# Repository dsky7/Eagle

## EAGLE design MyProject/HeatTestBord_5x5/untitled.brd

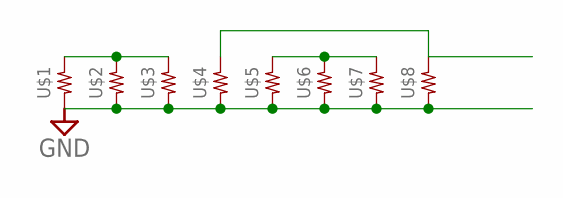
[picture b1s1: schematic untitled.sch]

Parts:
U$1, U$2, U$3, U$4, U$5, U$6, U$7, U$8: RESISTOR__SMD; 1608

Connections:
GND: U$1.1, U$2.1, U$3.1, U$4.1, U$5.1, U$6.1, U$7.1, U$8.1
unnamed: U$1.2, U$2.2, U$3.2
unnamed: U$5.2, U$6.2, U$7.2
unnamed: U$4.2, U$8.2

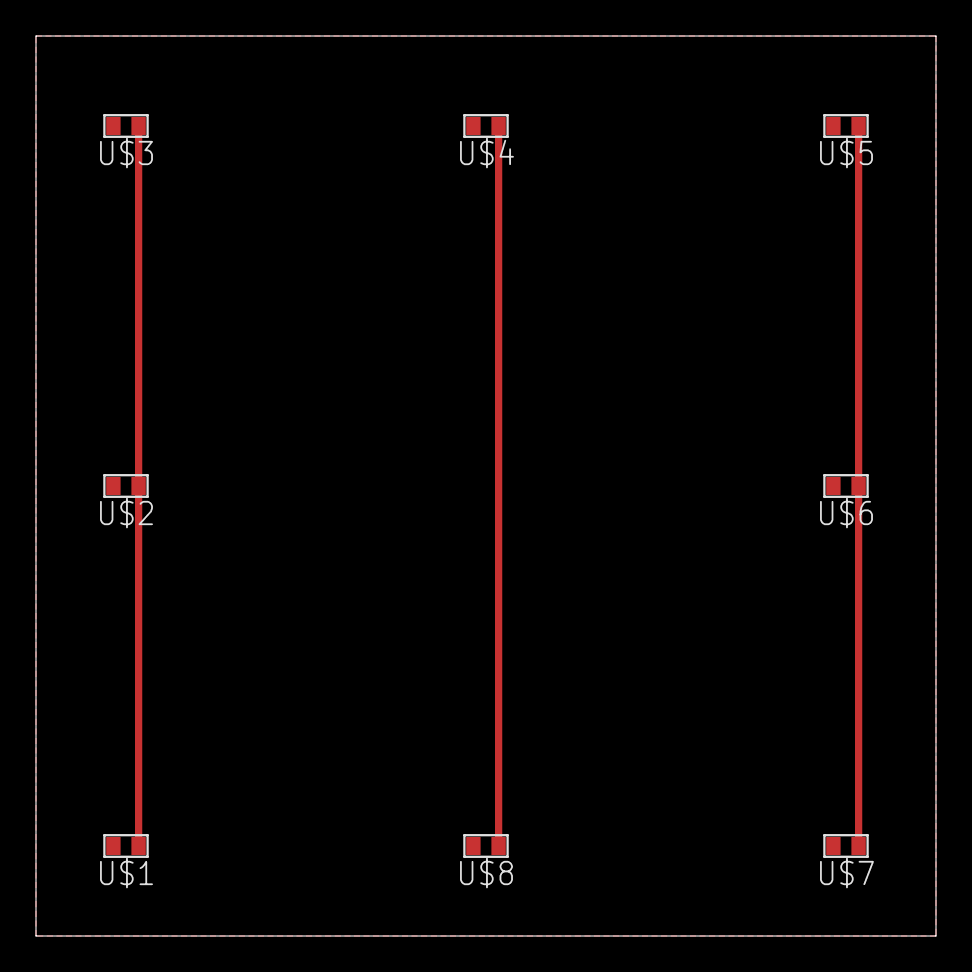
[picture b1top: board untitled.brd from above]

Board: 2 copper layers, 50.0 x 50.0 mm, 8 parts (0 on the bottom side), 4 nets.

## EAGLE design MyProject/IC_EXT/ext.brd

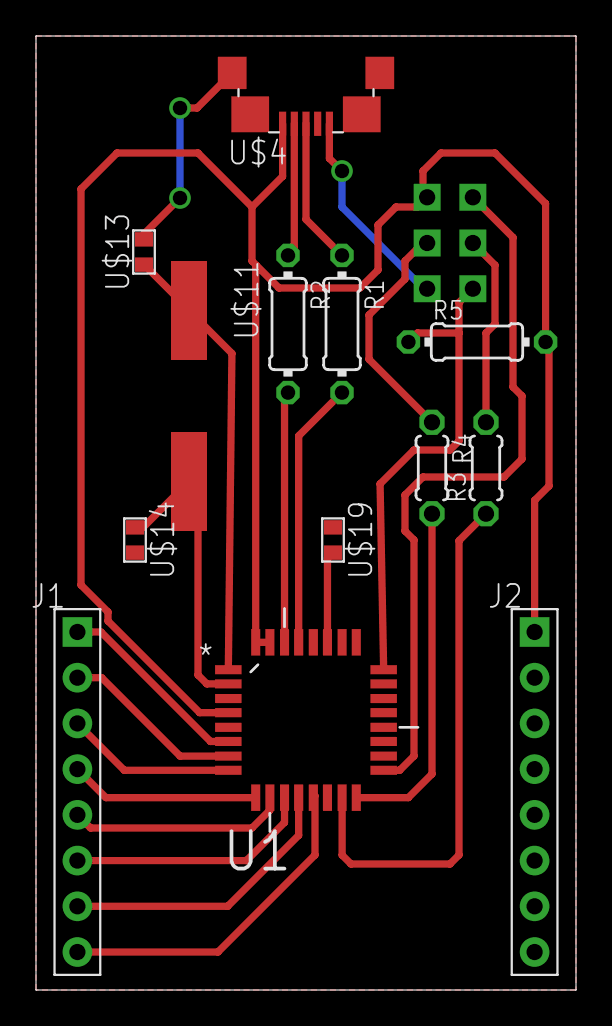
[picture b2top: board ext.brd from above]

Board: 2 copper layers, 30.0 x 53.0 mm, 14 parts (1 on the bottom side), 23 nets.

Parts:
J1, J2: 8P-2.54
R1, R2, R5: 0204/7
R3, R4: 0204/5
U1: ATMEGA32U2-AU; QFP80P900X900X120-32N
U$4: MICRO-USB-SHIELD-ZX62R-B-5P; ZX62R-B-5P
U$7: ICSP
U$11: CSM-7X-DU
U$13, U$14, U$19: 1608

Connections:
+5V: J2.1, R5.2, U1.4, U1.31, U1.32, U$4.1, U$7.2
D+: R1.1, U$4.3
D-: R2.1, U$4.2
GND: J2.2, U1.3, U1.28, U$4.5, U$4.M1, U$4.M2, U$4.M3, U$4.M4, U$7.6, U$13.P$2, U$14.P$2, U$19.P$1
MISO: U1.17, U$7.1
MOSI: R4.2, U1.16
unnamed: J1.2, U1.7
unnamed: J1.3, U1.8
unnamed: J1.4, U1.9
unnamed: J1.5, U1.10
unnamed: J1.6, U1.11
unnamed: J1.7, U1.12
unnamed: J1.8, U1.13
unnamed: J1.1, U1.6
unnamed: R1.2, U1.29
unnamed: R2.2, U1.30
unnamed: R3.2, U$7.3
unnamed: R4.1, U$7.4
unnamed: U1.27, U$19.P$2
RESET: R5.1, U1.24, U$7.5
SCLK: R3.1, U1.15
XTAL1: U1.1, U$11.1, U$13.P$1
XTAL2: U1.2, U$11.2, U$14.P$1

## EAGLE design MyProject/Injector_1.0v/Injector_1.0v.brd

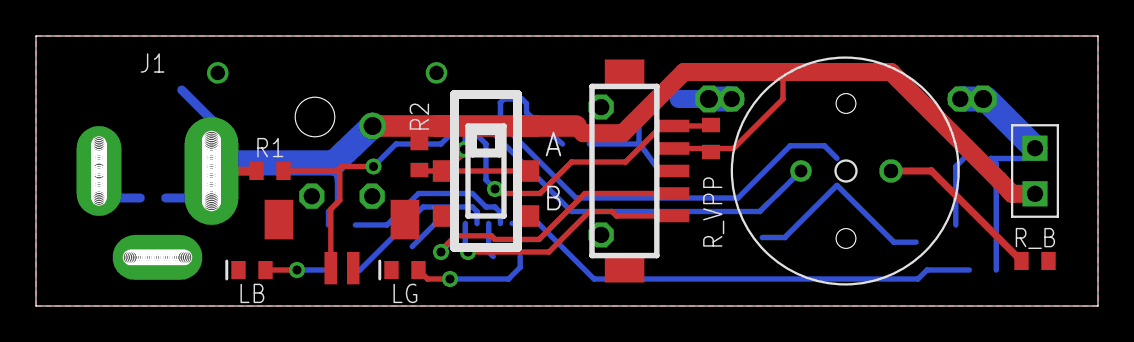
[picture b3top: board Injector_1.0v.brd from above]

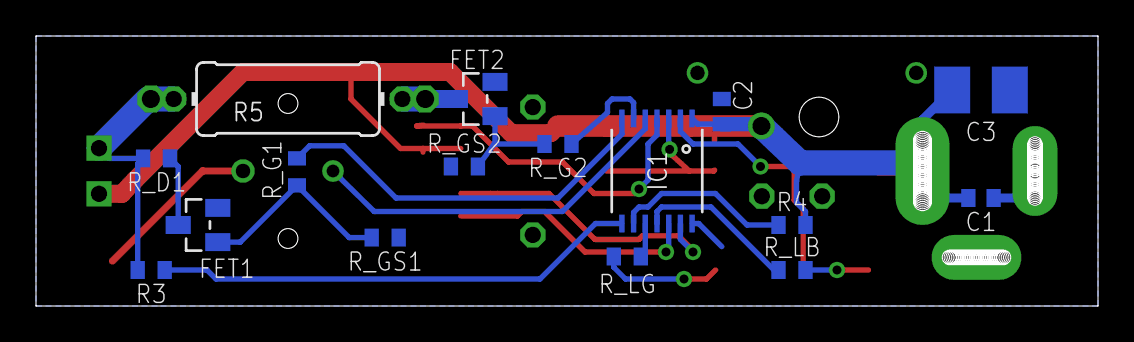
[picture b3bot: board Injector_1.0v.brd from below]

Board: 2 copper layers, 59.0 x 15.0 mm, 30 parts (17 on the bottom side), 22 nets.

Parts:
BUZZER: PKM13EPYH
C1, C2: 1608
C3: 3225
CN1: DF13-5P-1.25V; DF13C-5P-1.25V
CN2: DF13-2P-1.25V; DF13C-2P-1.25V
CN3: PIN_HEADER_2; PIN_HEADER_2S
DRILEGEND: DRILEGEND
FET1, FET2: CHIP_FET; SOT23
IC1: PIC16F1823; TSSOP
J1: 2DC-0005X; 2DC-0005D
LB: CHIPLED; 1608
LG: CHIPLED; 1608
R1, R2, R3, R4: 1608
R5: 0411/12
R6: P0613/15
R_B: 1608
R_D1: 1608
R_G1, R_G2: 1608
R_GS1, R_GS2: 1608
R_LB: 1608
R_LG: 1608
R_VPP: 1608
SW1: SSSS213202; SSSS2

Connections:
+5V: C1.P$2, C2.P$2, C3.P$2, CN1.P$2, CN3.P$2, IC1.1, J1.1, R1.2, R2.2, R4.1, R_VPP.2, SW1.1, SW1.1-
G1: IC1.7, R_G1.2
G2: IC1.6, R_G2.2
GND: C1.P$1, C2.P$1, C3.P$1, CN1.M$0, CN1.M$1, CN1.P$3, CN1.P$6, CN1.P$7, CN2.1, CN2.G1, CN2.G2, CN2.M$0, CN2.M$1, FET1.2, FET2.2, IC1.14, J1.2, LB.2, LG.2, R_B.1, R_GS1.2, R_GS2.2, SW1.3, SW1.3-
ICSP_CLK: CN1.P$5, IC1.12
ICSP_DATA: CN1.P$4, IC1.13
MCLR: CN1.P$1, IC1.4, R_VPP.1
unnamed: FET1.1, R_G1.1, R_GS1.1
unnamed: FET2.1, R_G2.1, R_GS2.1
unnamed: FET1.3, R_D1.2
unnamed: FET2.3, R5.1, R6.1
unnamed: BUZZER.P$1, IC1.5
unnamed: BUZZER.P$2, R_B.2
unnamed: CN2.2, IC1.2, R1.1
unnamed: IC1.8, R3.2
unnamed: IC1.9, R4.2
unnamed: LB.1, R_LB.1
unnamed: CN3.P$1, R3.1, R5.2, R6.2, R_D1.1
unnamed: LG.1, R_LG.1
RA2: IC1.11, R_LB.2
RA4: IC1.3, R2.1, SW1.2, SW1.2-
RC0: IC1.10, R_LG.2

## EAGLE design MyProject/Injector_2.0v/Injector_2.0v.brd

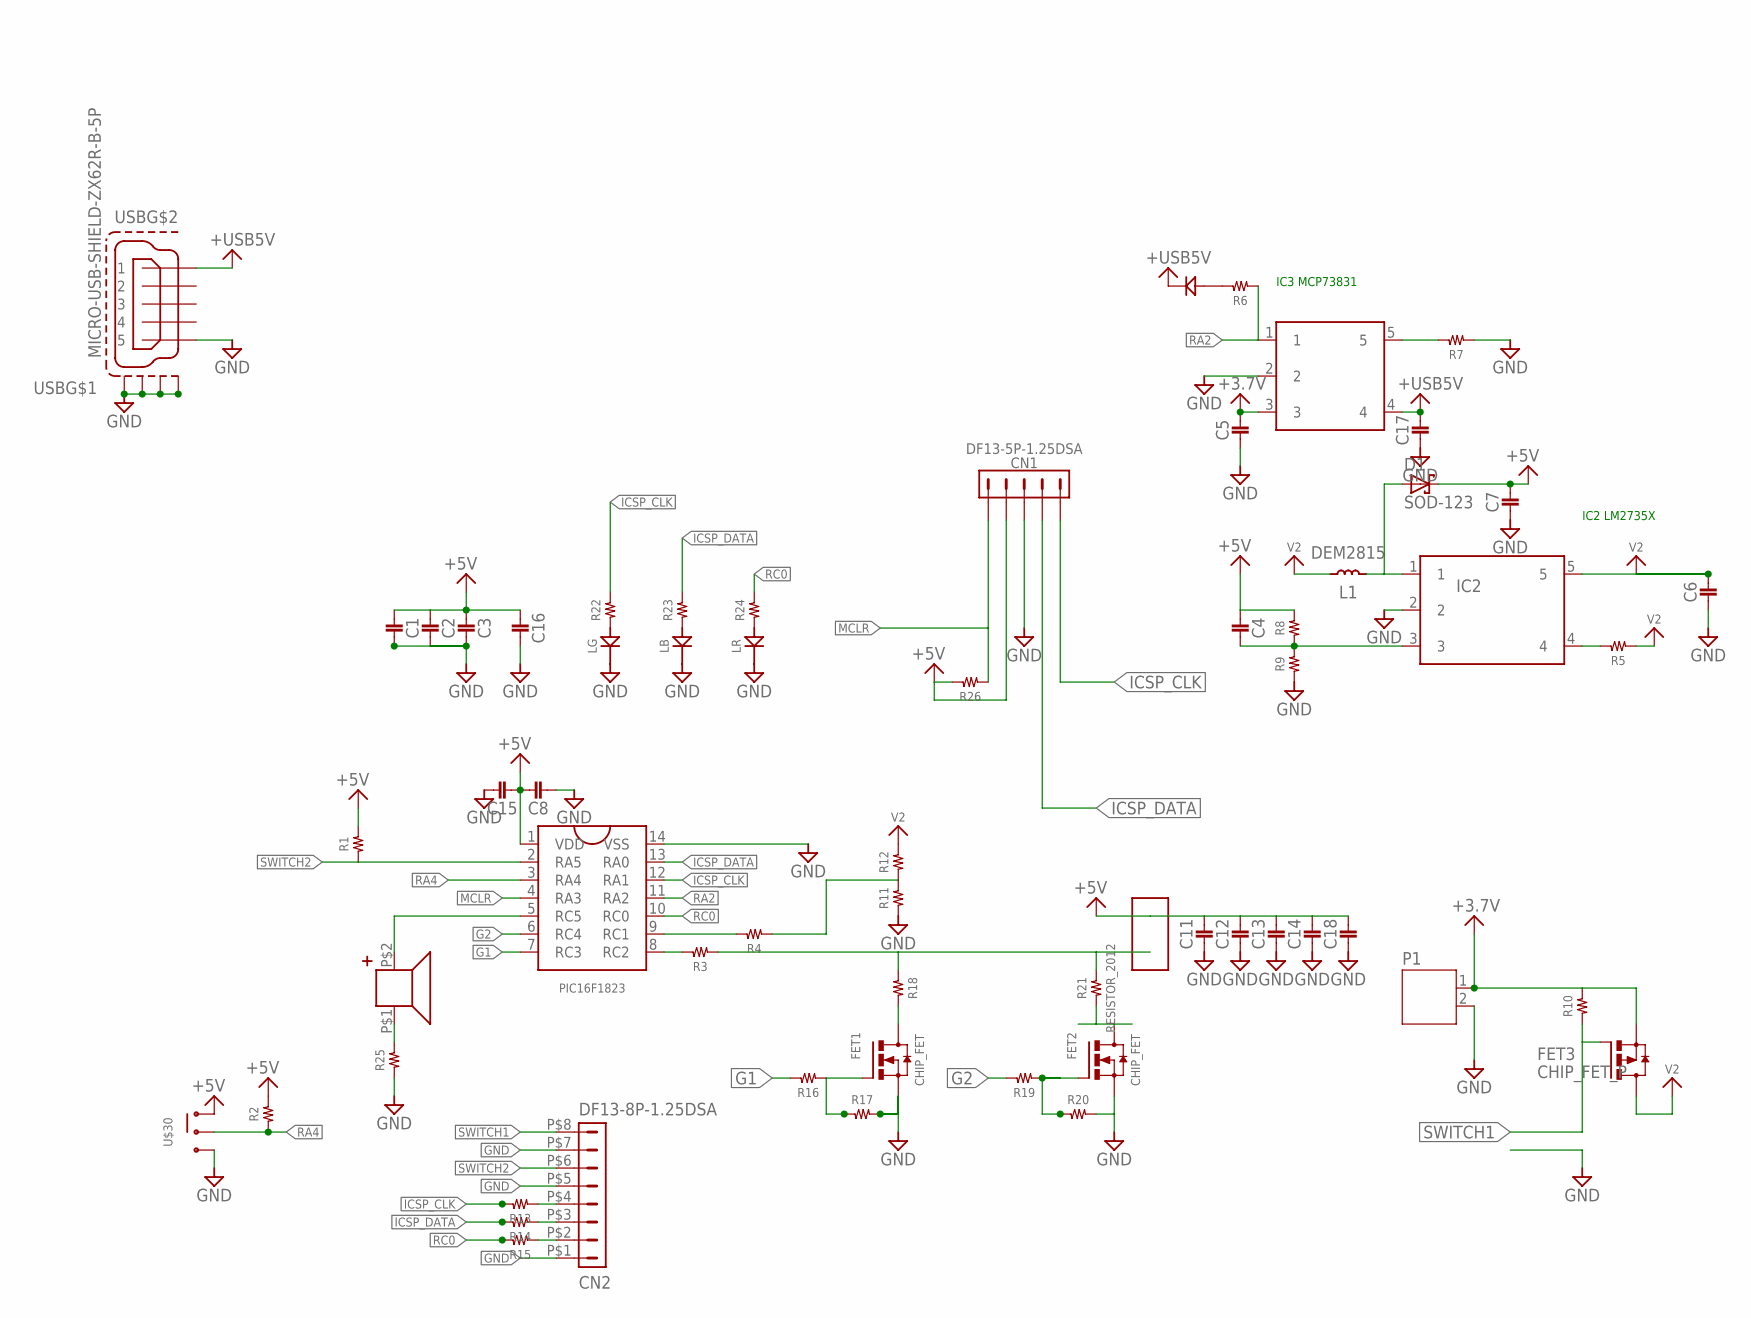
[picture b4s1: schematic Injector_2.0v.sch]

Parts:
C1, C2, C3, C4, C5, C6, C7, C8, C11, C12, C13, C14, C15, C16, C17, C18: 1608
CN1: DF13-5P-1.25DSA
CN2: DF13-8P-1.25DSA
D1: SOD-123; SOD_123
FET1, FET2: CHIP_FET; SOT23
FET3: CHIP_FET_P; SOT23
IC1: PIC16F1823; TSSOP
IC2: LM2735; SOT23-5L
IC3: MCP73831; SOT23-5L
L1: DEM2815
LB: CHIPLED; 1608
LG: CHIPLED; 1608
LR: CHIPLED; 1608
P1: JST-PH2
R1, R2, R3, R4, R5, R6, R7, R8, R9, R10, R11, R12, R13, R14, R15, R16, R17, R18, R19, R20, R22, R23, R24, R25, R26: RESISTOR__SMD; 1608
R21: RESISTOR_2012; 2012
ST: 1608
U$15: PKLCS1212E4001
U$16: PIN_HEADER_2_LARGE; PIN_HEADER_2S_LARGE
U$30: SS12D01G4
USB: MICRO-USB-SHIELD-ZX62R-B-5P; ZX62R-B-5P

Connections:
+3.7V: C5.P$1 (1), FET3.2 (S), IC3.3, P1.1, R10.2
+5V: C1.P$2 (2), C2.P$2 (2), C3.P$2 (2), C4.P$2 (2), C7.P$1 (1), C8.P$1 (1), C11.P$1 (1), C12.P$1 (1), C13.P$1 (1), C14.P$1 (1), C15.P$2 (2), C16.P$1 (1), C18.P$1 (1), CN1.P$2 (2), D1.C, IC1.1 (VDD), R1.2, R2.2, R8.2, R26.2, U$16.P$2, U$30.1
+USB5V: C17.P$1 (1), IC3.4, ST.2 (K), USB.1
G1: IC1.7 (RC3), R16.2
G2: IC1.6 (RC4), R19.2
GND: C1.P$1 (1), C2.P$1 (1), C3.P$1 (1), C5.P$2 (2), C6.P$2 (2), C7.P$2 (2), C8.P$2 (2), C11.P$2 (2), C12.P$2 (2), C13.P$2 (2), C14.P$2 (2), C15.P$1 (1), C16.P$2 (2), C17.P$2 (2), C18.P$2 (2), CN1.P$3 (3), CN2.P$1 (1), CN2.P$5 (5), CN2.P$7 (7), FET1.2 (S), FET2.2 (S), IC1.14 (VSS), IC2.2, IC3.2, LB.2 (K), LG.2 (K), LR.2 (K), P1.2, R7.1, R9.1, R11.1, R17.2, R20.2, R25.1, U$30.3, USB.5, USB.M1 (S1), USB.M2 (S2), USB.M3 (S3), USB.M4 (S4)
ICSP_CLK: CN1.P$5 (5), IC1.12 (RA1), R13.2, R22.2
ICSP_DATA: CN1.P$4 (4), IC1.13 (RA0), R14.2, R23.2
MCLR: CN1.P$1 (1), IC1.4 (RA3), R26.1
unnamed: FET1.1 (G), R16.1, R17.1
unnamed: FET2.1 (G), R19.1, R20.1
unnamed: FET1.3 (D), R18.2
unnamed: FET2.3 (D), R21.1
unnamed: IC1.5 (RC5), U$15.P$2 (PLUS)
unnamed: R25.2, U$15.P$1 (MINUS)
unnamed: IC1.8 (RC2), R3.2
unnamed: IC1.9 (RC1), R4.2
unnamed: LG.1 (A), R22.1
unnamed: R3.1, R18.1, R21.2, U$16.P$1
unnamed: LB.1 (A), R23.1
unnamed: D1.A, IC2.1, L1.P$2 (2)
unnamed: IC3.5, R7.2
unnamed: LR.1 (A), R24.1
unnamed: C4.P$1 (1), IC2.3, R8.1, R9.2
unnamed: IC2.4, R5.2
unnamed: R4.1, R11.2, R12.1
unnamed: CN2.P$4 (4), R13.1
unnamed: CN2.P$3 (3), R14.1
unnamed: CN2.P$2 (2), R15.1
unnamed: R6.2, ST.1 (A)
RA2: IC1.11 (RA2), IC3.1, R6.1
RA4: IC1.3 (RA4), R2.1, U$30.2
RC0: IC1.10 (RC0), R15.2, R24.2
SWITCH1: CN2.P$8 (8), FET3.1 (G), R10.1
SWITCH2: CN2.P$6 (6), IC1.2 (RA5), R1.1
V2: C6.P$1 (1), FET3.3 (D), IC2.5, L1.P$1 (1), R5.1, R12.2

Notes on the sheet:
IC3 MCP73831
IC2 LM2735X

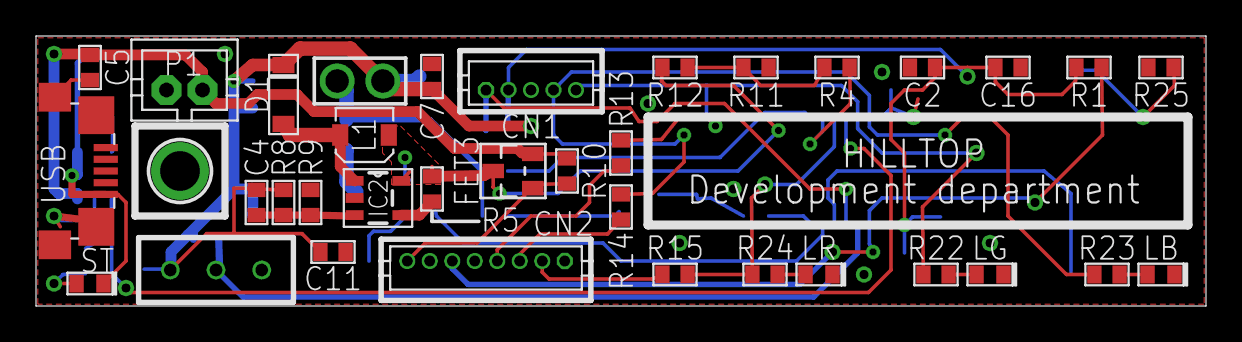
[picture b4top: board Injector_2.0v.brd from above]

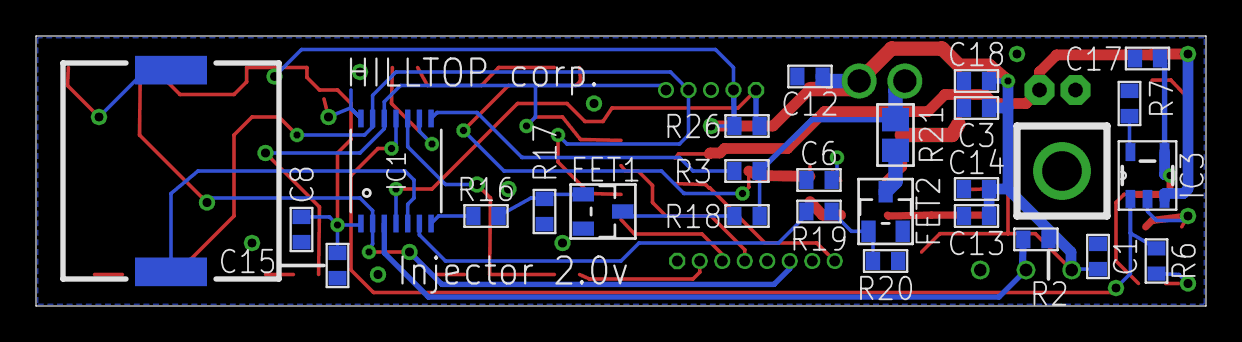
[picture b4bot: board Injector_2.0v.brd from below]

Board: 2 copper layers, 65.0 x 15.0 mm, 62 parts (26 on the bottom side), 36 nets.

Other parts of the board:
DRILEGEND: DRILEGEND

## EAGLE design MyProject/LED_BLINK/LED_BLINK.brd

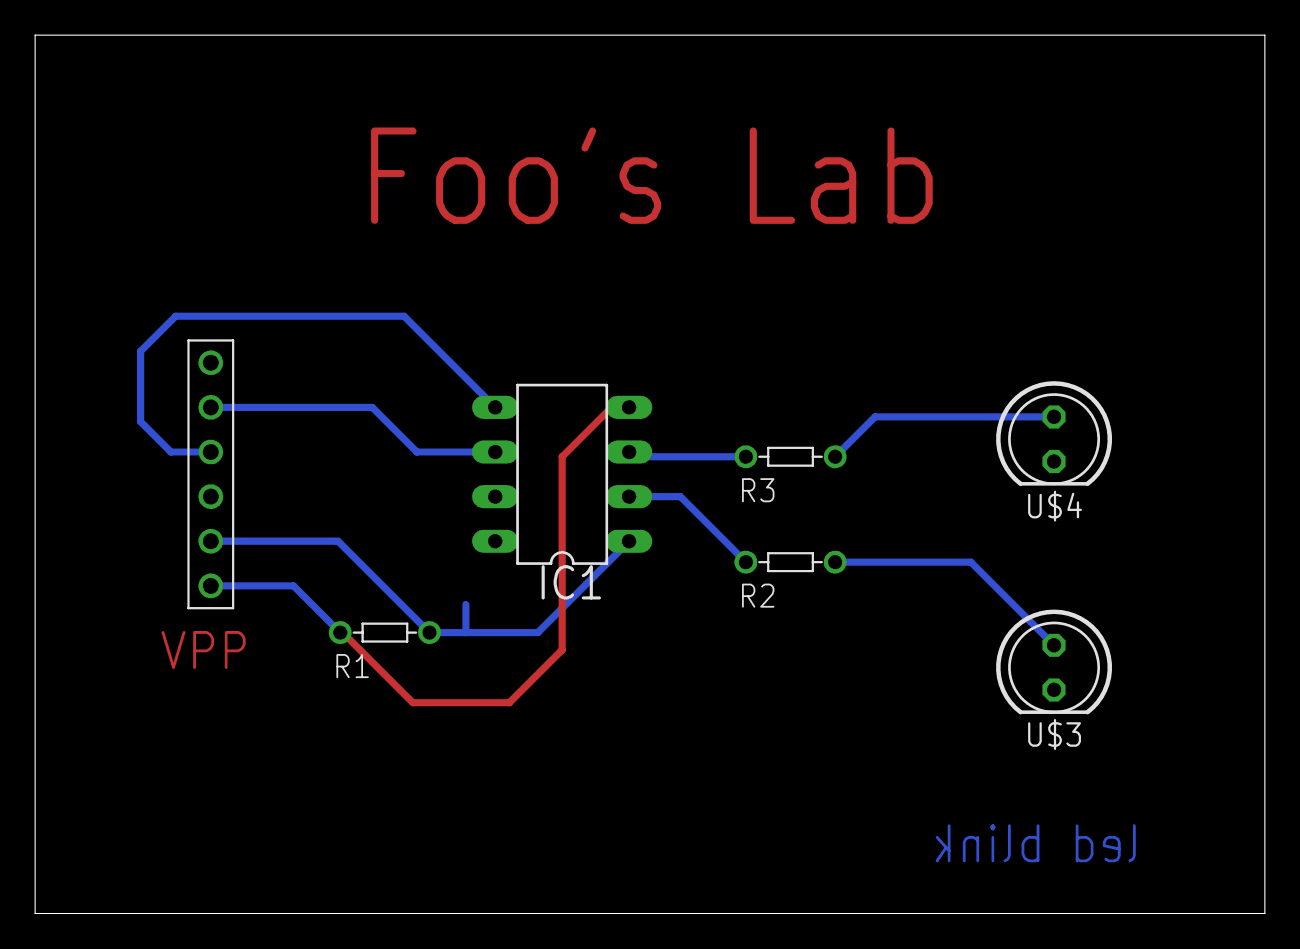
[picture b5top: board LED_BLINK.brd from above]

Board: 2 copper layers, 70.0 x 50.0 mm, 8 parts (1 on the bottom side), 9 nets.

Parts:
IC1: PIC12F683P; DIL8
R1, R2, R3: 1/8R
U$3, U$4: 5MMLED; 5MM
U$9: 1608
U$11: PIN_HEADER_6

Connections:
+5V: IC1.1, R1.P$2, U$9.P$1, U$11.2
CLK: IC1.6, U$11.5
DAT: IC1.5, U$11.4
GND: IC1.8, U$3.K, U$4.K, U$9.P$2, U$11.3
unnamed: R2.P$2, U$3.A
unnamed: R3.P$2, U$4.A
unnamed: IC1.2, R2.P$1
unnamed: IC1.3, R3.P$1
VPP: IC1.4, R1.P$1, U$11.1

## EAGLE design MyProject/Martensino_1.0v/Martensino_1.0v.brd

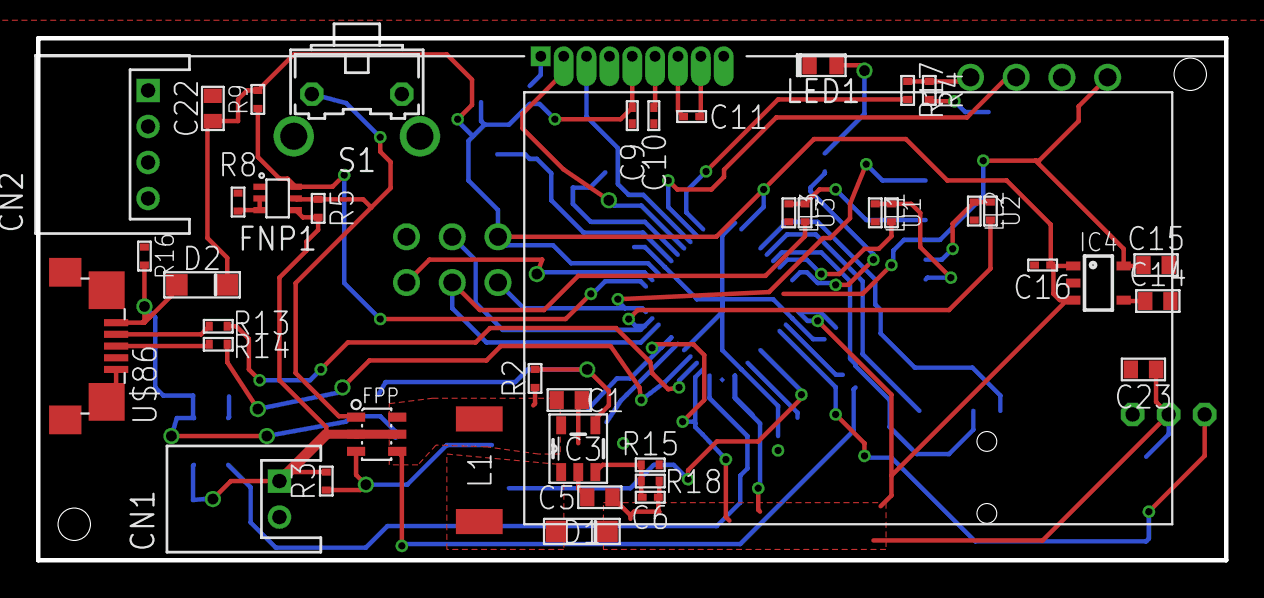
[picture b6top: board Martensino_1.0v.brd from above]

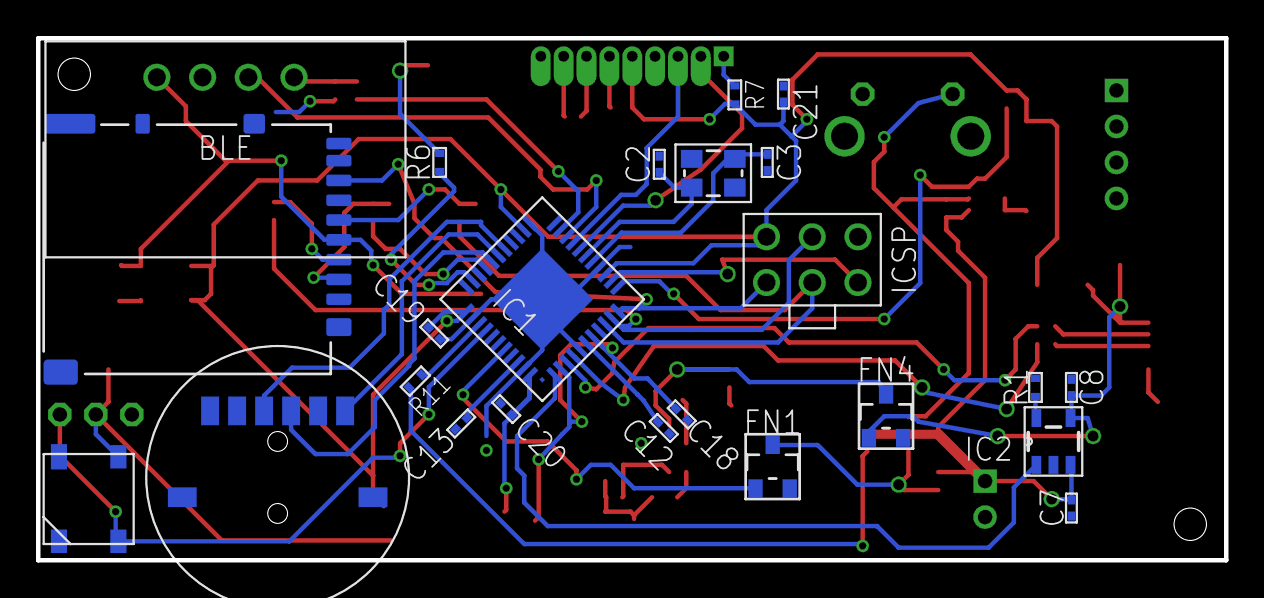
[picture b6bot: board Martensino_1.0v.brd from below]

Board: 2 copper layers, 66.0 x 29.0 mm, 68 parts (24 on the bottom side), 49 nets.

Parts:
BLE: BLE_SERIAL2_NO_HOLE; BLESERIAL2_NO_HOLE
C1, C5: 22uF; 1608
C2, C3: 10pF; 1005
C6: 1nF; 1005
C7, C8: 4.7uF; 1005
C9, C10, C11: 1005
C12, C16: 1uF; 1005
C13, C18, C19, C20, C21: 0.1uF; 1005
C14: 0.01uF; 1608
C15, C23: 10uF; 1608
C22: 47uF; 1608
CN1: S2B-PH-K-S
CN2: S4B-PH-K-S
D1, D2: SOD-123; SOD_123
FN1, FN4: CHIP_FET; SOT23
FNP1: SI1553CDL; SOT363
FPP: FDC6506P; SOT23-6
IC1: ATMEGA32U4; QFN-44-7X7
IC2: MCP73831; SOT23-5L
IC3: LM2735; SOT23-5L
IC4: TAR5SB; SSOP5-P-0.95
L1: D63; TOKO
LED1: CHIPLED; 1608
LED2: NEO_FLAT
LL1: 3k; 1005
LL2, LL3: 3K; 1005
R1: 2K; 1005
R2: 100K; 1005
R3, R5, R8, R9, R15, R16: 10K; 1005
R4: 1.5k; 1005
R6: 330; 1005
R7: RESISTOR_1005; 1005
R11, R17: 1K; 1005
R13, R14: 22; 1005
R18: 30k; 1005
S1: B3F-31XX
U1, U3: 2K; 1005
U2: 2k; 1005
U$3: ICSP
U$8: LIPO400MAH
U$30: 3PIN_HALF; 3PIN_INT_HALF
U$45: DM3AT-SF-PEJ
U$68: LCD_I2C_AQM; AQM1602
U$86: MICRO-USB-KYORITU; ZX62R-B-5P
U$90: TMHU28
XTAL: FA-238

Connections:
+3.3V: BLE.4, C15.P$1, IC4.5, U$45.4
+3.7V: C1.P$1, FPP.4, FPP.6, IC3.5, L1.1, R2.2, R11.2
+5V: C5.P$1, C6.1, C9.1, C16.1, C18.1, C19.1, C20.1, C21.1, C22.P$1, C23.P$1, D1.C, D2.C, IC1.2, IC1.7, IC1.14, IC1.24, IC1.34, IC1.44, IC4.1, IC4.3, LED2.1, R7.2, R9.2, R18.2, U$3.2, U$30.2, U$68.P$5
+USB5V: C8.1, D2.A, FN4.1, IC2.4, R16.2, U$86.5
A1: IC1.37, LED2.4, U$30.3
A4: FN1.1, IC1.40
ADC0: IC1.36, R11.1
ATOM: BLE.1, R4.2, R17.1
D0: BLE.2, IC1.20
D1: IC1.21, R17.2
D2: IC1.19, U$68.P$3
D3: IC1.18, U$68.P$2
D6: IC1.27, U$90.3
D7: IC1.1, IC2.1
D8: IC1.28, U$90.1
D9: IC1.29, U$90.T
D10: IC1.30, U1.2
D11: FNP1.6, IC1.12, R9.1
D13: IC1.32, R6.2
D+: R14.2, U$86.3
D-: R13.2, U$86.4
DL: D1.A, IC3.1, L1.2
FB: C6.2, IC3.3, R15.2, R18.1
GND: BLE.3, C1.P$2, C2.2, C3.2, C5.P$2, C7.2, C8.2, C9.2, C10.2, C12.1, C13.2, C14.P$2, C15.P$2, C16.2, C18.2, C19.2, C20.2, C21.2, C22.P$2, C23.P$2, CN1.2, FN1.2, FN4.2, FNP1.1, IC1.5, IC1.15, IC1.23, IC1.35, IC1.43, IC1.TH, IC2.2, IC3.2, IC4.2, LED1.2, LED2.3, LL1.2, LL2.2, LL3.2, R1.1, R4.1, R8.1, R15.1, R16.1, S1.1, U$3.6, U$30.1, U$45.6, U$45.GND1, U$45.GND2, U$45.GND3, U$45.GND4, U$68.P$4, U$86.1, U$86.M1, U$86.M2, U$86.M3, U$86.M4, U$90.C, XTAL.2, XTAL.4
MISO: IC1.11, U$3.1, U$45.7
MOSI: IC1.10, U2.2, U$3.4
unnamed: LED1.1, R6.1
unnamed: IC2.5, R1.2
unnamed: FN4.3, IC3.4, R2.1
unnamed: R7.1, U$68.P$1
unnamed: LL3.1, U3.1, U$45.5
unnamed: FN1.3, FPP.3, R3.1
unnamed: C3.1, IC1.16, XTAL.1
unnamed: IC1.3, R13.1
unnamed: C13.1, IC1.42
unnamed: C2.1, IC1.17, XTAL.3
unnamed: LL2.1, U2.1, U$45.3
unnamed: LL1.1, U1.1, U$45.2
unnamed: C12.2, IC1.6
unnamed: IC1.4, R14.1
unnamed: C14.P$1, IC4.4
unnamed: C10.1, U$68.P$6
unnamed: C11.1, U$68.P$7
unnamed: C11.2, U$68.P$8
RESET: IC1.13, U$3.5
SCLK: IC1.9, U3.2, U$3.3
SIG: FNP1.2, FNP1.3, R8.2
SWSIG: FNP1.5, FPP.1, R5.1, S1.2
V2: C7.1, CN1.1, FNP1.4, FPP.2, FPP.5, IC2.3, R3.2, R5.2

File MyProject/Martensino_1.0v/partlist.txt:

Partlist

Exported from Martensino_1.0v.brd at 2016/03/08 19:01

EAGLE Version 7.5.0 Copyright (c) 1988-2015 CadSoft

Assembly variant: 

Part     Value               Package            Library      Position (mm)         Orientation

BLE      BLE_SERIAL2_NO_HOLE BLESERIAL2_NO_HOLE 12_module    (30 5)                MR0
C1       22uF                1608               02_C         (25.5 13.1)           MR180
C2       10pF                1005               02_C         (43.7 3.9)            MR270
C3       10pF                1005               02_C         (49.5 3.9)            MR90
C5       22uF                1608               02_C         (27.2 18.5)           MR0
C6       1nF                 1005               02_C         (30 18.5)             MR0
C7       4.7uF               1005               02_C         (12.4 13.9)           R270
C8       4.7uF               1005               02_C         (15.2 14)             R180
C12      1uF                 1005               02_C         (43.45 18.85)         R0
C13      0.1uF               1005               02_C         (37 16.7)             MR45
C14      0.01uF              1608               02_C         (22.65 7.5)           R180
C15      10uF                1608               02_C         (22.7 5.9)            R180
C16      1uF                 1005               02_C         (28.6 7.2)            R270
C18      0.1uF               1005               02_C         (38.4 5.05)           MR225
C19      0.1uF               1005               02_C         (38.7 16.7)           MR315
C20      0.1uF               1005               02_C         (35 12.7)             MR135
C21      0.1uF               1005               02_C         (46.8 7.6)            MR270
C22      47uF                1608               02_C         (3.5 5.6)             MR0
C23      10uF                1608               02_C         (56.5 16)             MR180
CN1                          JST-PH2            jst-ph (1)   (10 16.2)             MR270
D1       SOD-123             SOD_123            15_DIODE     (26.2 20.4)           MR180
D2       SOD-123             SOD_123            15_DIODE     (7.9 7.7)             R180
FN1      CHIP_FET            SOT23              06_FET       (15.4 6.4)            MR0
FN4      CHIP_FET            SOT23              06_FET       (21.6 16.7)           R0
FNP1     SI1553CDL           SOT363             06_FET       (33.8 7)              R270
FPP      FDC6506P            SOT23-6            06_FET       (14.8 15)             MR90
IC1      ATMEGA32U4          QFN-44-7X7         04_IC        (40.5 11)             MR315
IC2      MCP73831            SOT23-5L           04_IC        (15.1 16.5)           R270
IC3      LM2735              SOT23-5L           04_IC        (26 15.8)             MR180
IC4      TAR5SB              SSOP5-P-0.95       04_IC        (26.2 6.8)            R90
L1       D63                 TOKO               03_L         (20.5 17)             MR90
LED1     CHIPLED             1608               10_LED       (27 11)               R90
LED2     NEO_FLAT            NEO_FLAT           10_LED       (56.5 11)             MR270
LED3     NEO_FLAT            NEO_FLAT           10_LED       (3.5 11)              MR90
R1       2K                  1005               01_R         (17.6 17)             R90
R2       100K                1005               01_R         (25.7 16.1)           R270
R3       10K                 1005               01_R         (13 11.2)             MR270
R4       1.5k                1005               01_R         (37.1 3.2)            MR180
R5       10K                 1005               01_R         (36.25 6.25)          R270
R6       330                 1005               01_R         (29.6 9.4)            MR180
R8       10K                 1005               01_R         (31.8 6.8)            R270
R9       10K                 1005               01_R         (34.8 5.8)            MR225
R11      1K                  1005               01_R         (34.95 14.55)         MR45
R13      22                  1005               01_R         (40.7 17.1)           R180
R14      22                  1005               01_R         (40.7 16.2)           R180
R15      10K                 1005               01_R         (30 16.7)             MR0
R16      10K                 1005               01_R         (20.5 3.4)            R270
R17      1K                  1005               01_R         (40.7 3.2)            R0
R18      30k                 1005               01_R         (30 17.6)             MR180
SW2      SKRPACE010          SKRP               09_1_switch  (41 11)               R270
U$3      ICSP                ICSP               08_CONECTOR  (49.3 16)             MR90
U$8      3PIN_HALF           3PIN_INT_HALF      08_CONECTOR  (3.5 16)              R0
U$30     3PIN_HALF           3PIN_INT_HALF      08_CONECTOR  (56.5 6)              R180
U$68     LCD_I2C_AQM         AQM1602            12_module    (33 28)               R0
U$69     1005                1005               02_C         (36.3 24.65)          R0
U$70     RESISTOR_1005       1005               01_R         (-7.65 -11.7)         R0
U$81     1005                1005               02_C         (-6.55 -15)           R0
U$85     1005                1005               02_C         (-6.55 -19.55)        R0
U$86     MICRO-USB-KYORITU   ZX62R-B-5P         con-hirose1  (1.75 12.8)           R0
XTAL     FA-238              FA-238             09_2_CRYSTAL (46.5 4.5)            MR0
